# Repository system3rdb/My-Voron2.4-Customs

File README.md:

# My Voron2.4 Customs
 My Voron2.4 Customs

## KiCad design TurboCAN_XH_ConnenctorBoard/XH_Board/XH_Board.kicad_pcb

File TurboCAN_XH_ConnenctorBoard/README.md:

24v pin

turbocan data pin

some 5v pin

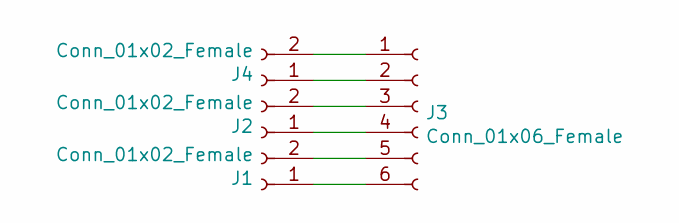
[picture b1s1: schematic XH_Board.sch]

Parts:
J1, J2, J4: Conn_01x02_Female; JST_XH_B2B-XH-A_1x02_P2.50mm_Vertical
J3: Conn_01x06_Female; JST_XH_B6B-XH-A_1x06_P2.50mm_Vertical

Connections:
unnamed: J1.1, J3.6
unnamed: J1.2, J3.5
unnamed: J2.1, J3.4
unnamed: J2.2, J3.3
unnamed: J3.1, J4.2
unnamed: J3.2, J4.1

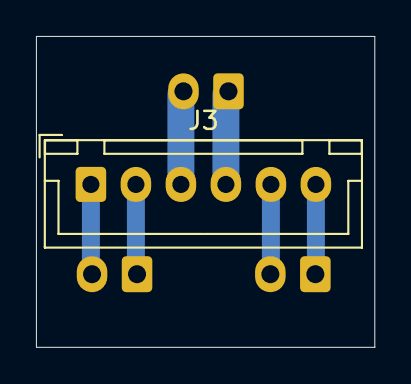
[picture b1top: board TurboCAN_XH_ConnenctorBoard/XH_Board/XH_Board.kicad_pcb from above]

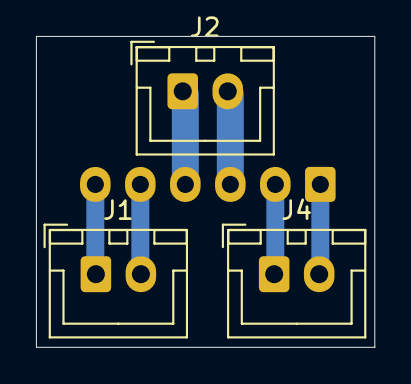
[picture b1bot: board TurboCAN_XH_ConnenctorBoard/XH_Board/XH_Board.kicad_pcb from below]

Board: 2 copper layers, 18.8 x 17.3 mm, 4 parts (3 on the bottom side), 6 nets.

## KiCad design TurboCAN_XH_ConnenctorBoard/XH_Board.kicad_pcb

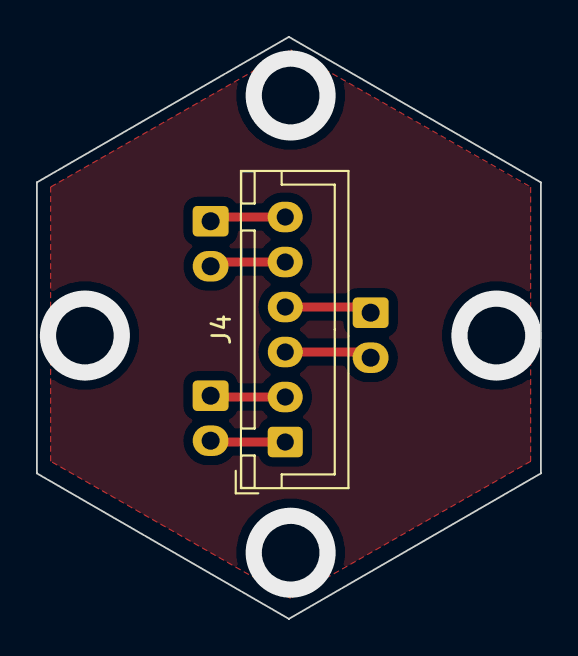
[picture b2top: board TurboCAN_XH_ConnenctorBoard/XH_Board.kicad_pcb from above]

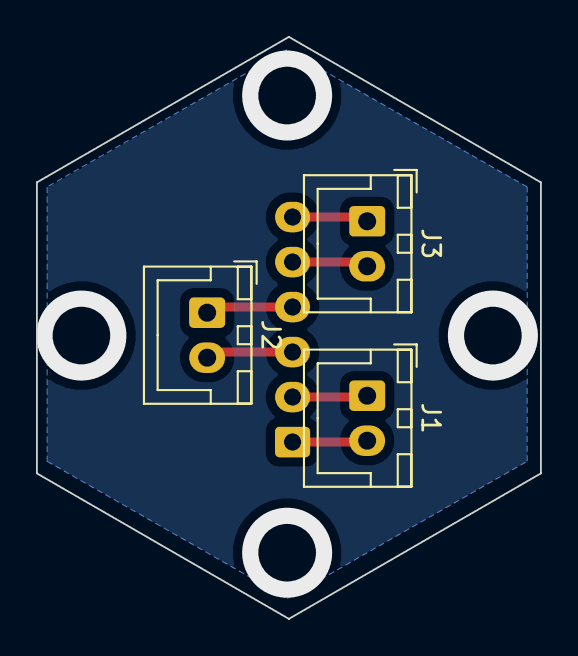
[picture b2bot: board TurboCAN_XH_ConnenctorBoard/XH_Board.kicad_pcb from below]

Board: 2 copper layers, 28.0 x 32.3 mm, 4 parts (3 on the bottom side), 6 nets.

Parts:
J1, J2, J3: Conn_01x02; JST_XH_B2B-XH-A_1x02_P2.50mm_Vertical
J4: Conn_01x06; JST_XH_B6B-XH-A_1x06_P2.50mm_Vertical

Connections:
unnamed: J1.1, J4.2
unnamed: J1.2, J4.1
unnamed: J2.1, J4.4
unnamed: J2.2, J4.3
unnamed: J3.1, J4.6
unnamed: J3.2, J4.5

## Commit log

2021-09-30 Update and rename README to PanelLaver
2021-09-30 Update PanelLaver
2021-09-30 chane name
2021-09-30 TurboCan Mount
    TurboCan Mount for galileo extruder
2021-09-30 Include Panel Locker Step file
2021-09-30 create step folder
2021-10-02 lift handle step files
2021-10-02 step file upload
2021-10-02 create folder
2021-10-04 rework pcb
2021-10-11 practice some
